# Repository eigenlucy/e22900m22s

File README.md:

# e22900m22s

[SX1262 22dBm LoRa Transciever](https://www.lcsc.com/product-detail/LoRa-Modules_Chengdu-Ebyte-Elec-Tech-E22-900M22S_C411293.html)

Created by lucy moglia <eigenlucy@proton.me>

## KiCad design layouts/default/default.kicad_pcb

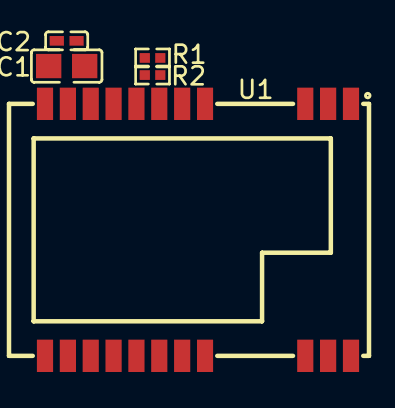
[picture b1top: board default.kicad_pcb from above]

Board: 2 copper layers, 5 parts (0 on the bottom side), 4 nets, no tracks yet.

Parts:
C1: 10µF ±10% 25V X5R; C0805-3b2e55
C2: 100nF ±10% 16V X7R; C0402-b3ef17
R1, R2: 1kΩ ±1% 62.5mW; R0402-56259e
U1: WIRELM-SMD_E22-900M22S-72e54e

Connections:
RXEN: R1.2, U1.6
TXEN: R2.2, U1.7
VCC: C1.1, C2.1, R1.1, R2.1, U1.9
gnd: C1.2, C2.2, U1.1, U1.2, U1.3, U1.4, U1.5, U1.10, U1.11, U1.12, U1.20, U1.22

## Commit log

2025-05-05 added release.yml
2025-05-05 fixed pinout
2025-05-05 fixed email
2025-05-05 frozen
2025-05-20 updated SPI interface
